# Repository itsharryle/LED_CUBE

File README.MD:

# 8x8x8 LED CUBE

Figure 1. A demo of the LED Cube in action.

Figure 2. Underlaying circuit of the LED Cube.

Figure 3. Connections between power supply, Arduino, and circuit.

# DESCRIPTION
Some time ago I stumbled upon a youtube video showcasing an awesome LED cube that displays animations in 3D. I was intrigued. I searched the internet for a tutorial and found a post on [instructable](https://www.instructables.com/id/Led-Cube-8x8x8/). Coincidentally, the author of the article is the same person who made the youtube video. This gave me the inspiration to make my own. There is a problem, though, that this tutorial requires too many components and some of which are difficult to find. I told myself, "There must be an easier way!". As a result, I came up with my own design using only a few common components. In fact, you might have most of the components for this project if you bought an Arduino Starter Kit or some similar kits. Of course, this design is not the safest, nor production quality, but it's intended to be that way. This project, after all, is a DIY toy I made to fulfill my crave of making things. You can buy an LED Cube kit on eBay for about 2-3 times cheaper than what it costs to make it this way. The only thing you'll learn from those kits, however, is how to solder and that's it. The PCB has all the traces required. The micro-controller is pre-programmed and you don't even need to know anything about electronics to put it together. With that being said, this project is not easy. You'll run into problems and **Google** will be your best friend. I recommend learning basic electronics and understand how the cube works before you attempt to build one. Also, check out my [video](https://www.youtube.com/watch?v=T5Aq7cRc-mU) if you haven't. Good luck!

# FILES AND FOLDERS

- **CUBE** - This folder contains the Arduino code file.

    - **CUBE.ino** - Arduino code file.

- **CUBE+SCHEMATIC.schdoc** - SCHDOC Schematic file. To be used with schematic editors.

- **CUBE-SCHEMATIC.pdf** - Printable PDF schematic file.

- **LED Cube PCB Board V.6.brd** - PCB file. To be used with circuit board editors. Made by _Michael McDermott_.

- **LED Cube PCB Board V.6.sch** - SCH schematic file. To be used with schematic editors. Made by _Michael McDermott_.

- **LICENSE** - Standard MIT Licensing information.

- **SN74HC595.pdf** - Shift register data sheet for reference.

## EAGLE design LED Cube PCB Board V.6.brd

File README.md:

# LED_CUBE

8x8x8 LED cube powered by an Arduino

Making-of on Youtube: https://www.youtube.com/watch?v=T5Aq7cRc-mU

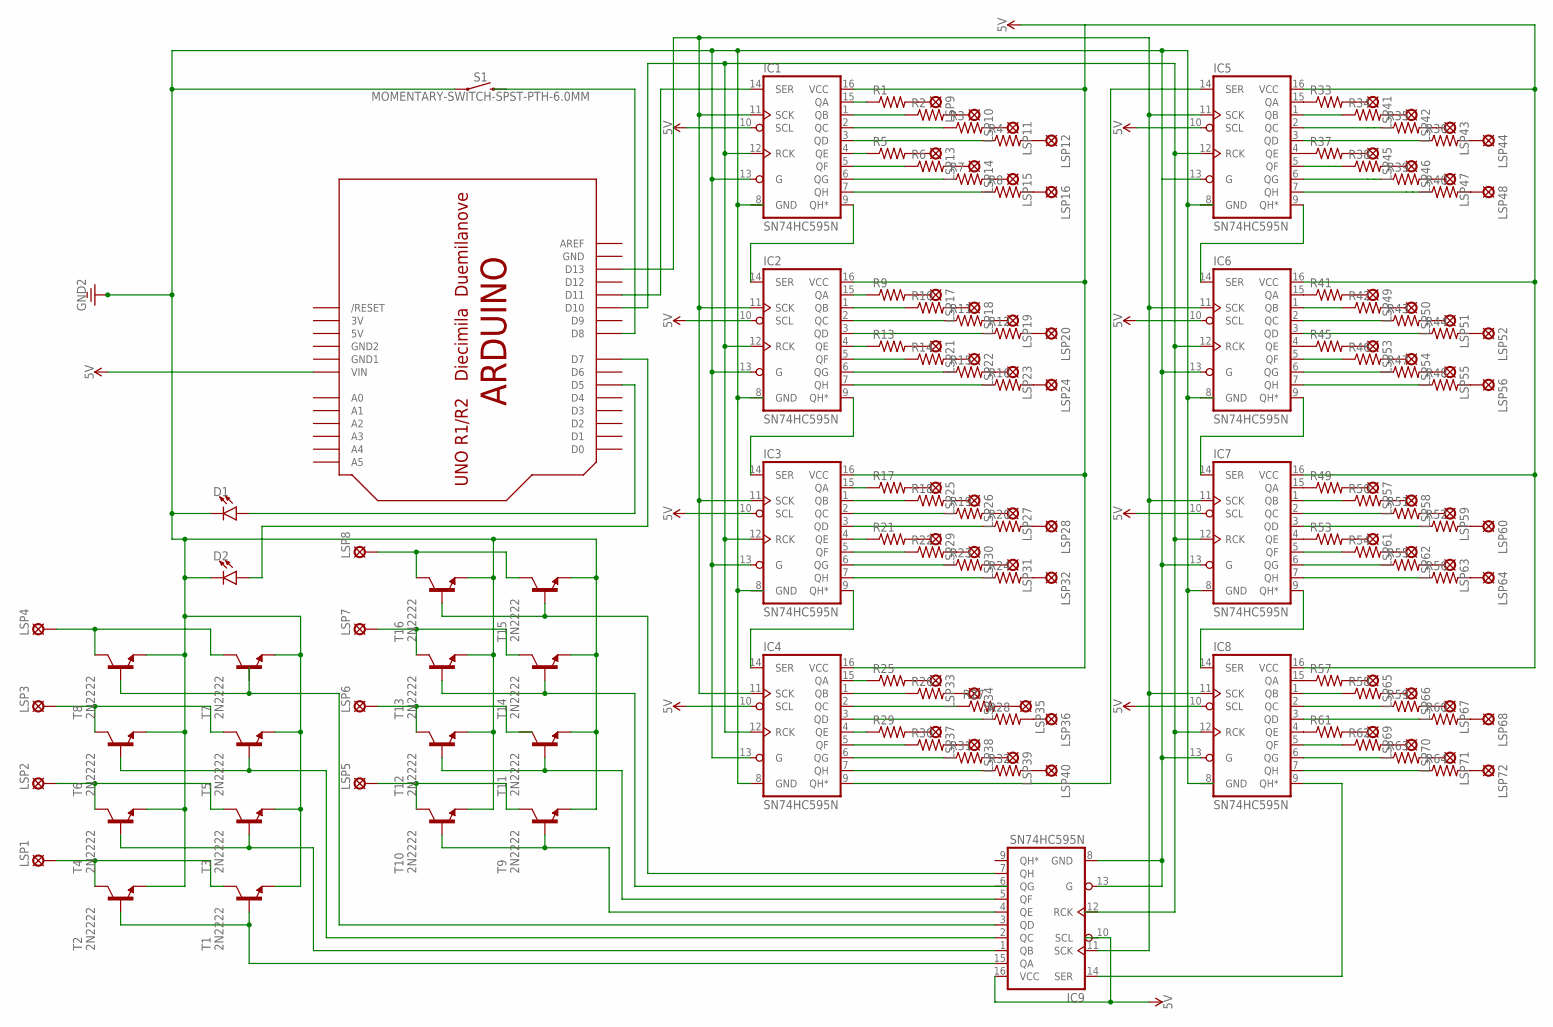
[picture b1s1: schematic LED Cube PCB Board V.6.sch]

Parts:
D1, D2: LED-3MM-NO_SILK; LED_3MM-NS
IC1, IC2, IC3, IC4, IC5, IC6, IC7, IC8, IC9: SN74HC595N; DIP16
LSP1, LSP2, LSP3, LSP4, LSP5, LSP6, LSP7, LSP8: LSP10
LSP9, LSP10, LSP11, LSP12, LSP13, LSP14, LSP15, LSP16, LSP17, LSP18, LSP19, LSP20, LSP21, LSP22, LSP23, LSP24, LSP25, LSP26, LSP27, LSP28, LSP29, LSP30, LSP31, LSP32, LSP33, LSP34, LSP35, LSP36, LSP37, LSP38, LSP39, LSP40, LSP41, LSP42, LSP43, LSP44, LSP45, LSP46, LSP47, LSP48, LSP49, LSP50, LSP51, LSP52, LSP53, LSP54, LSP55, LSP56, LSP57, LSP58, LSP59, LSP60, LSP61, LSP62, LSP63, LSP64, LSP65, LSP66, LSP67, LSP68, LSP69, LSP70, LSP71, LSP72: LSP11
R1, R2, R3, R4, R5, R6, R7, R8, R9, R10, R11, R12, R13, R14, R15, R16, R17, R18, R19, R20, R21, R22, R23, R24, R25, R26, R27, R28, R29, R30, R31, R32, R33, R34, R35, R36, R37, R38, R39, R40, R41, R42, R43, R44, R45, R46, R47, R48, R49, R50, R51, R52, R53, R54, R55, R56, R57, R58, R59, R60, R61, R62, R63, R64: R-US_0204/5; 0204/5
S1: MOMENTARY-SWITCH-SPST-PTH-6.0MM; TACTILE_SWITCH_PTH_6.0MM
T1, T2, T3, T4, T5, T6, T7, T8, T9, T10, T11, T12, T13, T14, T15, T16: 2N2222; TO92-EBC-OVAL
U$1: ARDUINO-NOHOLE

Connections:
3V: U$1.3V
5V: IC1.10 (SCL), IC1.16 (VCC), IC2.16 (VCC), IC3.16 (VCC), IC4.16 (VCC), IC5.10 (SCL), IC5.16 (VCC), IC6.10 (SCL), IC6.16 (VCC), IC7.10 (SCL), IC7.16 (VCC), IC8.10 (SCL), IC8.16 (VCC), IC9.10 (SCL), IC9.16 (VCC), U$1.5V, U$1.VIN
GND: D1.K (C), D2.K (C), IC1.8 (GND), IC1.13 (G), IC2.8 (GND), IC2.13 (G), IC3.8 (GND), IC3.13 (G), IC4.8 (GND), IC4.13 (G), IC5.8 (GND), IC5.13 (G), IC6.8 (GND), IC6.13 (G), IC7.8 (GND), IC7.13 (G), IC8.8 (GND), IC8.13 (G), IC9.8 (GND), IC9.13 (G), S1.1, T1.E, T2.E, T3.E, T4.E, T5.E, T6.E, T7.E, T8.E, T9.E, T10.E, T11.E, T12.E, T13.E, T14.E, T15.E, T16.E, U$1.GND
GND1: U$1.GND1
GND2: U$1.GND2
unnamed: IC1.7 (QH), R8.1
unnamed: IC1.6 (QG), R7.1
unnamed: IC1.5 (QF), R6.1
unnamed: IC1.4 (QE), R5.1
unnamed: IC1.3 (QD), R4.1
unnamed: IC1.2 (QC), R3.1
unnamed: IC1.1 (QB), R2.1
unnamed: IC1.15 (QA), R1.1
unnamed: LSP9.MP, R1.2
unnamed: LSP10.MP, R2.2
unnamed: LSP11.MP, R3.2
unnamed: LSP12.MP, R4.2
unnamed: LSP13.MP, R5.2
unnamed: LSP14.MP, R6.2
unnamed: LSP15.MP, R7.2
unnamed: LSP16.MP, R8.2
unnamed: IC6.1 (QB), R42.1
unnamed: IC6.2 (QC), R43.1
unnamed: IC6.3 (QD), R44.1
unnamed: IC6.5 (QF), R46.1
unnamed: IC6.6 (QG), R47.1
unnamed: IC6.7 (QH), R48.1
unnamed: IC8.1 (QB), R58.1
unnamed: IC8.2 (QC), R59.1
unnamed: IC8.3 (QD), R60.1
unnamed: IC8.5 (QF), R62.1
unnamed: IC8.6 (QG), R63.1
unnamed: IC8.7 (QH), R64.1
unnamed: IC9.7 (QH), T15.B, T16.B
unnamed: T13.B, T14.B
unnamed: IC9.5 (QF), T11.B, T12.B
unnamed: IC9.4 (QE), T9.B, T10.B
unnamed: IC2.7 (QH), R16.1
unnamed: IC2.6 (QG), R15.1
unnamed: IC2.5 (QF), R14.1
unnamed: IC2.4 (QE), R13.1
unnamed: IC2.3 (QD), R12.1
unnamed: IC2.2 (QC), R11.1
unnamed: IC2.1 (QB), R10.1
unnamed: IC2.15 (QA), R9.1
unnamed: IC5.15 (QA), R33.1
unnamed: IC5.4 (QE), R37.1
unnamed: IC6.15 (QA), R41.1
unnamed: IC6.4 (QE), R45.1
unnamed: IC8.15 (QA), R57.1
unnamed: IC8.4 (QE), R61.1
unnamed: IC7.4 (QE), R53.1
unnamed: IC7.15 (QA), R49.1
unnamed: IC4.1 (QB), R26.1
unnamed: IC4.15 (QA), R25.1
unnamed: LSP17.MP, R9.2
unnamed: IC4.2 (QC), R27.1
unnamed: LSP18.MP, R10.2
unnamed: IC4.3 (QD), R28.1
unnamed: IC4.4 (QE), R29.1
unnamed: IC4.5 (QF), R30.1
unnamed: IC3.1 (QB), R18.1
unnamed: IC4.6 (QG), R31.1
unnamed: IC4.7 (QH), R32.1
unnamed: LSP19.MP, R11.2
unnamed: LSP20.MP, R12.2
unnamed: LSP21.MP, R13.2
unnamed: LSP22.MP, R14.2
unnamed: LSP23.MP, R15.2
unnamed: IC3.7 (QH), R24.1
unnamed: IC3.6 (QG), R23.1
unnamed: IC3.5 (QF), R22.1
unnamed: IC3.4 (QE), R21.1
unnamed: IC3.3 (QD), R20.1
unnamed: IC3.2 (QC), R19.1
unnamed: LSP24.MP, R16.2
unnamed: IC3.15 (QA), R17.1
unnamed: LSP25.MP, R17.2
unnamed: LSP26.MP, R18.2
unnamed: LSP27.MP, R19.2
unnamed: LSP28.MP, R20.2
unnamed: LSP29.MP, R21.2
unnamed: LSP30.MP, R22.2
unnamed: LSP31.MP, R23.2
unnamed: LSP32.MP, R24.2
unnamed: IC5.7 (QH), R40.1
unnamed: IC5.6 (QG), R39.1
unnamed: IC5.5 (QF), R38.1
unnamed: LSP33.MP, R25.2
unnamed: IC5.3 (QD), R36.1
unnamed: IC5.2 (QC), R35.1
unnamed: IC5.1 (QB), R34.1
unnamed: LSP34.MP, R26.2
unnamed: LSP35.MP, R27.2
unnamed: LSP36.MP, R28.2
unnamed: LSP37.MP, R29.2
unnamed: LSP38.MP, R30.2
unnamed: LSP39.MP, R31.2
unnamed: LSP40.MP, R32.2
unnamed: LSP41.MP, R33.2
unnamed: LSP42.MP, R34.2
unnamed: LSP43.MP, R35.2
unnamed: LSP44.MP, R36.2
unnamed: LSP45.MP, R37.2
unnamed: LSP46.MP, R38.2
unnamed: LSP47.MP, R39.2
unnamed: LSP48.MP, R40.2
unnamed: LSP49.MP, R41.2
unnamed: LSP50.MP, R42.2
unnamed: LSP51.MP, R43.2
unnamed: LSP52.MP, R44.2
unnamed: LSP53.MP, R45.2
unnamed: LSP54.MP, R46.2
unnamed: LSP55.MP, R47.2
unnamed: LSP56.MP, R48.2
unnamed: LSP57.MP, R49.2
unnamed: LSP58.MP, R50.2
unnamed: IC7.7 (QH), R56.1
unnamed: IC7.6 (QG), R55.1
unnamed: IC7.5 (QF), R54.1
unnamed: LSP59.MP, R51.2
unnamed: IC7.3 (QD), R52.1
unnamed: IC7.2 (QC), R51.1
unnamed: IC7.1 (QB), R50.1
unnamed: LSP60.MP, R52.2
unnamed: LSP61.MP, R53.2
unnamed: LSP62.MP, R54.2
unnamed: LSP63.MP, R55.2
unnamed: LSP64.MP, R56.2
unnamed: LSP65.MP, R57.2
unnamed: LSP66.MP, R58.2
unnamed: LSP67.MP, R59.2
unnamed: LSP68.MP, R60.2
unnamed: IC1.9 (QH*), IC2.14 (SER)
unnamed: IC5.9 (QH*), IC6.14 (SER)
unnamed: IC6.9 (QH*), IC7.14 (SER)
unnamed: IC2.9 (QH*), IC3.14 (SER)
unnamed: IC3.9 (QH*), IC4.14 (SER)
unnamed: IC7.9 (QH*), IC8.14 (SER)
unnamed: S1.3 (2), U$1.D8
unnamed: IC1.12 (RCK), IC2.12 (RCK), IC3.12 (RCK), IC4.12 (RCK), IC5.12 (RCK), IC6.12 (RCK), IC7.12 (RCK), IC8.12 (RCK), U$1.D10
unnamed: IC1.14 (SER), U$1.D11
unnamed: IC1.11 (SCK), IC2.11 (SCK), IC3.11 (SCK), IC4.11 (SCK), IC5.11 (SCK), IC6.11 (SCK), IC7.11 (SCK), IC8.11 (SCK), IC9.11 (SCK), U$1.D13
unnamed: IC8.9 (QH*), IC9.14 (SER)
unnamed: D1.A, U$1.D5
unnamed: IC9.1 (QB), T3.B, T4.B
unnamed: IC4.9 (QH*), IC5.14 (SER)
unnamed: IC9.2 (QC), T5.B, T6.B
unnamed: IC9.3 (QD), T8.B
unnamed: LSP69.MP, R61.2
unnamed: LSP70.MP, R62.2
unnamed: LSP71.MP, R63.2
unnamed: IC9.15 (QA), T1.B, T2.B
unnamed: LSP72.MP, R64.2
unnamed: D2.A, U$1.D7
unnamed: LSP3.MP, T5.C, T6.C
unnamed: LSP4.MP, T7.C, T8.C
unnamed: LSP2.MP, T3.C, T4.C
unnamed: LSP1.MP, T1.C, T2.C
unnamed: LSP8.MP, T15.C, T16.C
unnamed: LSP7.MP, T13.C, T14.C
unnamed: LSP6.MP, T12.C
unnamed: LSP5.MP, T9.C, T10.C

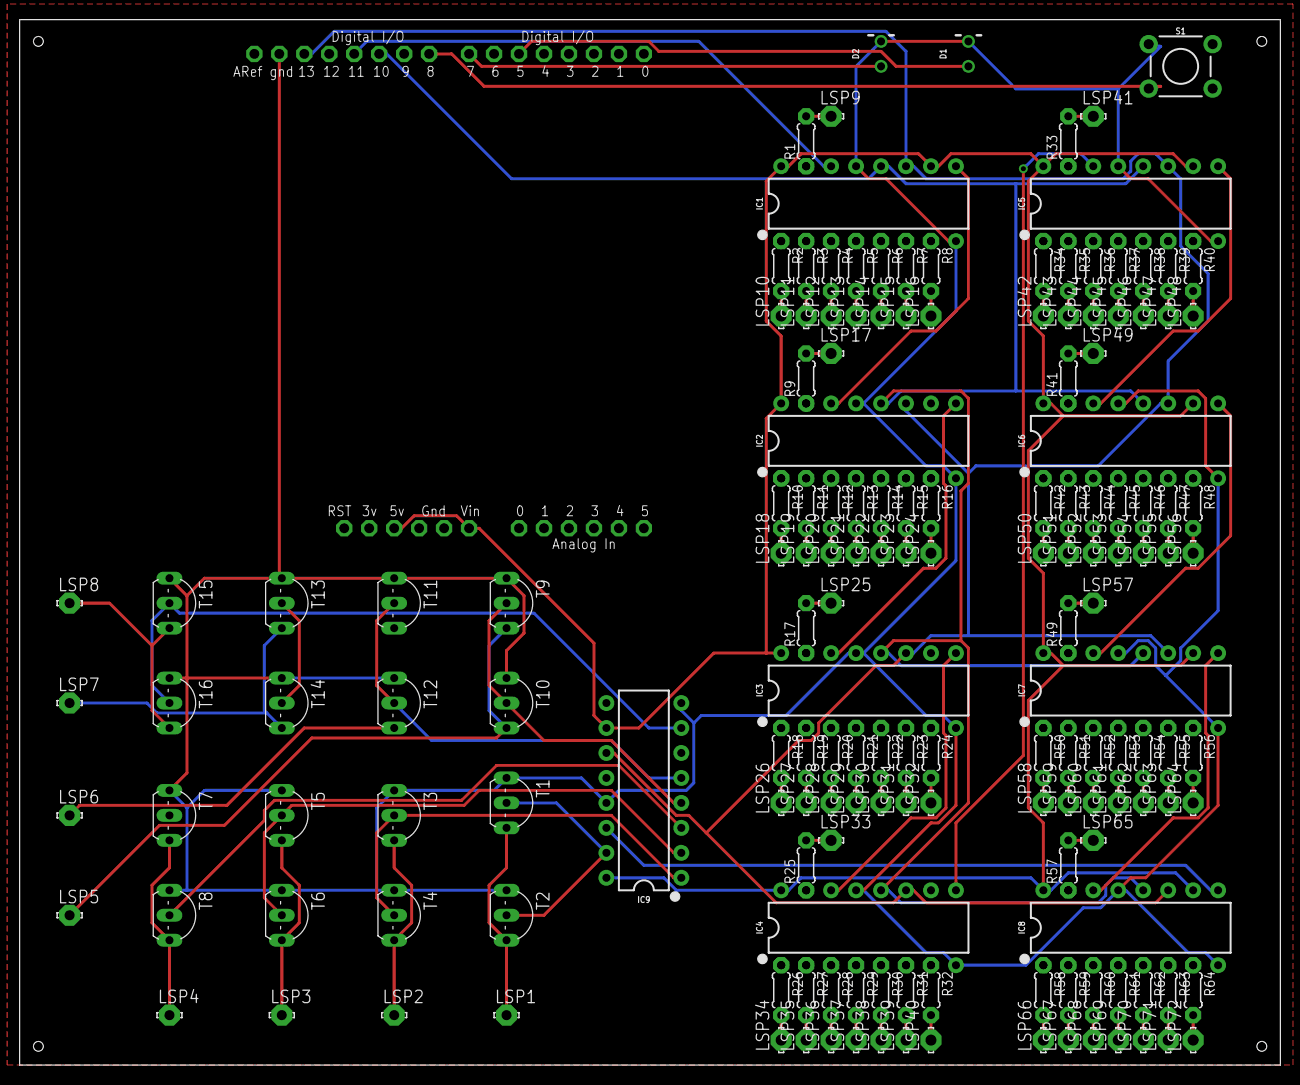
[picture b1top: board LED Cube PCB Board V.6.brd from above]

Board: 2 copper layers, 128.2 x 106.3 mm, 165 parts (0 on the bottom side), 160 nets.

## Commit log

2017-08-17 Updated schematic
2017-08-19 Update Schematic
    Added LEDs and switch
2017-08-31 8-31-17 UPDATE
    + Fixed layer numbers associated with shift registers.
    + Added data sheet for SN74HC595 shift register
2017-09-07 Revised cube-schematic
    + Fixed error on OE pin
    + Added VCC pin
    + Added SRCLR pin
2017-11-02 Add SCHDOC
    + SCHDOC can be imported into EasyEDA for easy modification
2018-03-16 3/16/18 Update
    + Added a file for PCB (.brd)
    + Added another schematic file (.sch)
    Both are made by Michael McDermott
2018-10-04 :memo: initial readme
2018-10-04 :zap: png->jpg
2019-01-13 add readme
2019-06-25 added auto rotate functionality
2019-11-24 fixed closing bracket
2020-09-02 Create Untitled.rtf
    Nothing to s
2020-10-11 Update CUBE.ino
    tpye cast your string parameter in the function text to to (*char) " char pointer
2022-05-14 Improve efficiency
    Improve effect conversion efficiency (remove delay)
    and debounce

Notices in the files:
parts and their libraries:
SparkFun-LED: Licensing: Creative Commons ShareAlike 4.0 International - https://creativecommons.org/licenses/by-sa/4.0
